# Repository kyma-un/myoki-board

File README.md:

<div align="center">

<picture>
  <source media="(prefers-color-scheme: dark)" srcset="assets/myoki-logo-white.png">
  
</picture>

<p>
  <sub>MAKE YOUR OWN KALMAN IMPLEMENTATION</sub>
</p>

</div>

---

MYOKI es una IMU modular y de código abierto para aprender filtros de Kalman en la asignatura de **Sensores y Actuadores**. Está basada en MYOSA del IEEE Sensors Council.

<div align="center">
  
</div>

## Qué es MYOKI

MYOKI es un *stack* de tres PCB cuadradas de 38.1 mm que se apilan con conectores hembra de 2.54 mm:

| Capa | Proyecto KiCad | Componente principal | Función |
| --- | --- | --- | --- |
| Base | [`myoki-mini-esp32-base`](hardware/myoki-mini-esp32-base) | ESP32-C3 SuperMini | MCU, alimentación (5 V / 3.3 V) y bus I²C / SPI |
| Capa IMU | [`myoki-bmi160-layer`](hardware/myoki-bmi160-layer) | GY-BMI160 | Acelerómetro + giróscopo de 6 ejes |
| Capa magnetómetro | [`myoki-gy271-layer`](hardware/myoki-gy271-layer) | GY-271 | Magnetómetro de 3 ejes |

El dibujo de ejes de la tapa marca la orientación del sistema de referencia de la placa (**+X**, **+Y** y **+Z** saliendo de la placa).

<div align="center">

</div>

### Placa base ESP32-C3

<table>
  <tr>
    <td align="center"></td>
    <td align="center"></td>
  </tr>
  <tr>
    <td align="center"><sub>Ensamblada</sub></td>
    <td align="center"><sub>PCB desnuda</sub></td>
  </tr>
</table>

La base expone los dos buses a las capas de sensores:

| Conector | Pin 1 | Pin 2 | Pin 3 | Pin 4 |
| --- | --- | --- | --- | --- |
| **J1** (SPI) | MOSI | MISO | CS | GND |
| **J2** (I²C) | SDA | SCL | VCC | GND |

El ESP32-C3 SuperMini se monta con el puerto USB-C hacia el borde marcado en la serigrafía.

## Estructura del repositorio

```text
myoki-board/
├── assets/                     Logos y arte gráfico
│   ├── myoki-design-top.png    Diseño de la tapa (acrílico)
│   ├── myoki-logo-banner.png   Banner para documentación
│   ├── myoki-logo-white.png    Logo transparente para fondos oscuros
│   ├── myoki-logo-navy.png     Logo transparente para fondos claros
│   └── renders/                Renders de la carcasa y las PCB
├── hardware/                   Fuentes de diseño (KiCad 10)
│   ├── lib/                    Librería propia "myoky-lib"
│   │   ├── myoky-lib.kicad_sym     Símbolos
│   │   ├── myoky-lib.pretty/       Footprints
│   │   ├── myoky-lib.3dshapes/     Modelos 3D (STEP)
│   │   └── vendor/                 Archivos originales de los fabricantes
│   ├── myoki-mini-esp32-base/  PCB base con ESP32-C3
│   ├── myoki-bmi160-layer/     PCB del BMI160
│   └── myoki-gy271-layer/      PCB del GY-271
└── manufacturing/              Todo lo necesario para fabricar
    ├── bom/                    Lista de materiales (myoki-bom.xlsx)
    ├── gerbers/                Gerbers + drill por placa y .zip listos para enviar
    └── enclosure/              Carcasa: STL para impresión 3D y DXF para corte láser
```

## Cómo construir una MYOKI

### 1. Fabricar las PCB

Sube cada `.zip` de [`manufacturing/gerbers/`](manufacturing/gerbers) a tu fabricante (JLCPCB, PCBWay, etc.):

| Archivo | Placa |
| --- | --- |
| [`myoki-mini-esp32-base.zip`](manufacturing/gerbers/myoki-mini-esp32-base.zip) | Base ESP32-C3 |
| [`myoki-bmi160-layer.zip`](manufacturing/gerbers/myoki-bmi160-layer.zip) | Capa BMI160 |
| [`myoki-gy271-layer.zip`](manufacturing/gerbers/myoki-gy271-layer.zip) | Capa GY-271 |

Parámetros: 2 capas, FR-4, 1.6 mm, 38.1 × 38.1 mm.

### 2. Comprar los componentes

La lista completa, con costos y links de compra, está en [`manufacturing/bom/myoki-bom.xlsx`](manufacturing/bom/myoki-bom.xlsx). Resumen:

| Cant. | Componente | Placa |
| --- | --- | --- |
| 1 | ESP32-C3 SuperMini | Base |
| 1 | Módulo GY-BMI160 | Capa BMI160 |
| 1 | Módulo GY-271 | Capa GY-271 |
| 3 | Condensador 100 nF, 1206 | Base |
| 1 | Resistencia 330 Ω, 1206 | Base |
| 1 | LED rojo, 2010 (5025 métrico) | Base |
| 6 | Conector hembra 1×04, 2.54 mm | 2 por placa |
| 8 + 8 | Separadores y tornillos M3 | Stack |

### 3. Fabricar la carcasa

| Archivo | Proceso |
| --- | --- |
| [`base_plastic_v03.stl`](manufacturing/enclosure/base_plastic_v03.stl) | Impresión 3D, base |
| [`plastic_case_top.stl`](manufacturing/enclosure/plastic_case_top.stl) | Impresión 3D, tapa |
| [`acrylic_drawing.dxf`](manufacturing/enclosure/acrylic_drawing.dxf) | Corte láser en acrílico, con el [diseño de la tapa](assets/myoki-design-top.png) |

### 4. Ensamblar

1. Suelda los componentes SMD y el ESP32-C3 en la base.
2. Suelda los módulos GY-BMI160 y GY-271 en sus capas.
3. Apila las placas con los conectores de 2.54 mm y fíjalas con los separadores M3.
4. Monta el stack en la carcasa y cierra con la tapa de acrílico.

## Editar el diseño

Abre cualquier `.kicad_pro` dentro de [`hardware/`](hardware) con **KiCad 10**. Cada proyecto incluye sus propias `fp-lib-table` y `sym-lib-table`, que apuntan a `${KIPRJMOD}/../lib`, así que la librería `myoky-lib` y sus modelos 3D se cargan sin configuración extra.

---

<div align="center">

<sub>SUPPORTED BY KYMA UN · Licencia <a href="LICENSE">MIT</a> © 2026</sub>

</div>

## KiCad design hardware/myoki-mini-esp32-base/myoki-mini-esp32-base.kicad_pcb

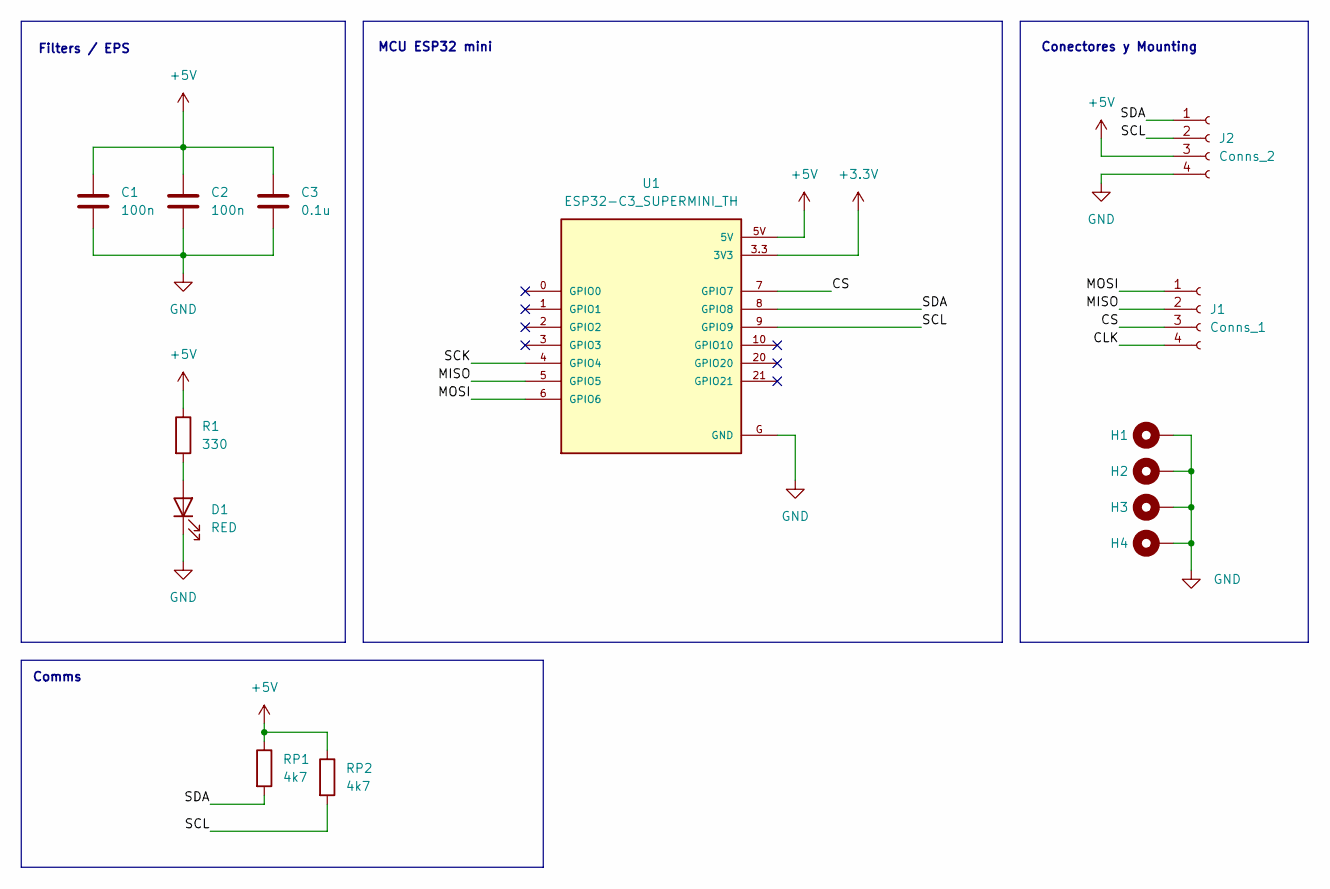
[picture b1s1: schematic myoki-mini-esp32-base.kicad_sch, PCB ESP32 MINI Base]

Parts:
C1, C2: 100n; C_1206_3216Metric_Pad1.33x1.80mm_HandSolder
C3: 0.1u; C_1206_3216Metric_Pad1.33x1.80mm_HandSolder
D1: RED; LED_2010_5025Metric_Pad1.52x2.65mm_HandSolder
H1, H2, H3, H4: MountingHole_Pad; MountingHole_3.2mm_M3_Pad_TopOnly
J1: Conns_1; PinSocket_1x04_P2.54mm_Vertical
J2: Conns_2; PinSocket_1x04_P2.54mm_Vertical
R1: 330; R_1206_3216Metric_Pad1.30x1.75mm_HandSolder
RP1, RP2: 4k7; R_1206_3216Metric_Pad1.30x1.75mm_HandSolder
U1: ESP32-C3_SUPERMINI_TH; MODULE_ESP32-C3_SUPERMINI_TH

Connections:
+3.3V: U1.3.3 (3V3)
+5V: C1.1, C2.1, C3.1, J2.3, R1.1, RP1.1, RP2.1, U1.5V
/CLK: J1.4
/CS: J1.3, U1.7 (GPIO7)
/MISO: J1.2, U1.5 (GPIO5)
/MOSI: J1.1, U1.6 (GPIO6)
/SCK: U1.4 (GPIO4)
/SCL: J2.2, RP2.2, U1.9 (GPIO9)
/SDA: J2.1, RP1.2, U1.8 (GPIO8)
GND: C1.2, C2.2, C3.2, D1.1 (K), H1.1 (1_1), H2.1 (1_1), H3.1 (1_1), H4.1 (1_1), J2.4, U1.G (GND)
unnamed: D1.2 (A), R1.2

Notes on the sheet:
MCU ESP32 mini
Conectores y Mounting
Filters / EPS
Comms

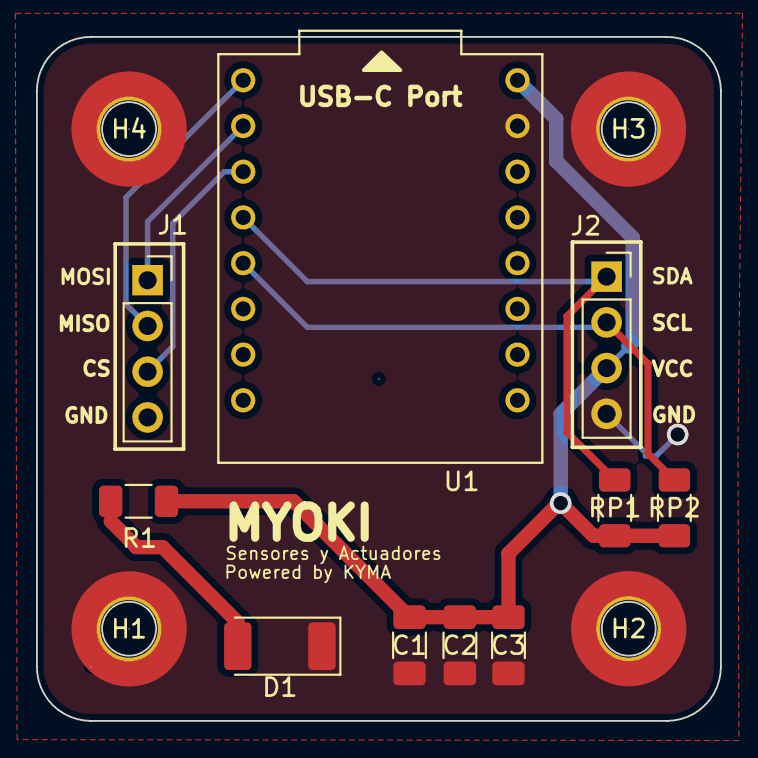
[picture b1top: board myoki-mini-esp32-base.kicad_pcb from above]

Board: 2 copper layers, 38.0 x 38.0 mm, 14 parts (0 on the bottom side), 8 nets.

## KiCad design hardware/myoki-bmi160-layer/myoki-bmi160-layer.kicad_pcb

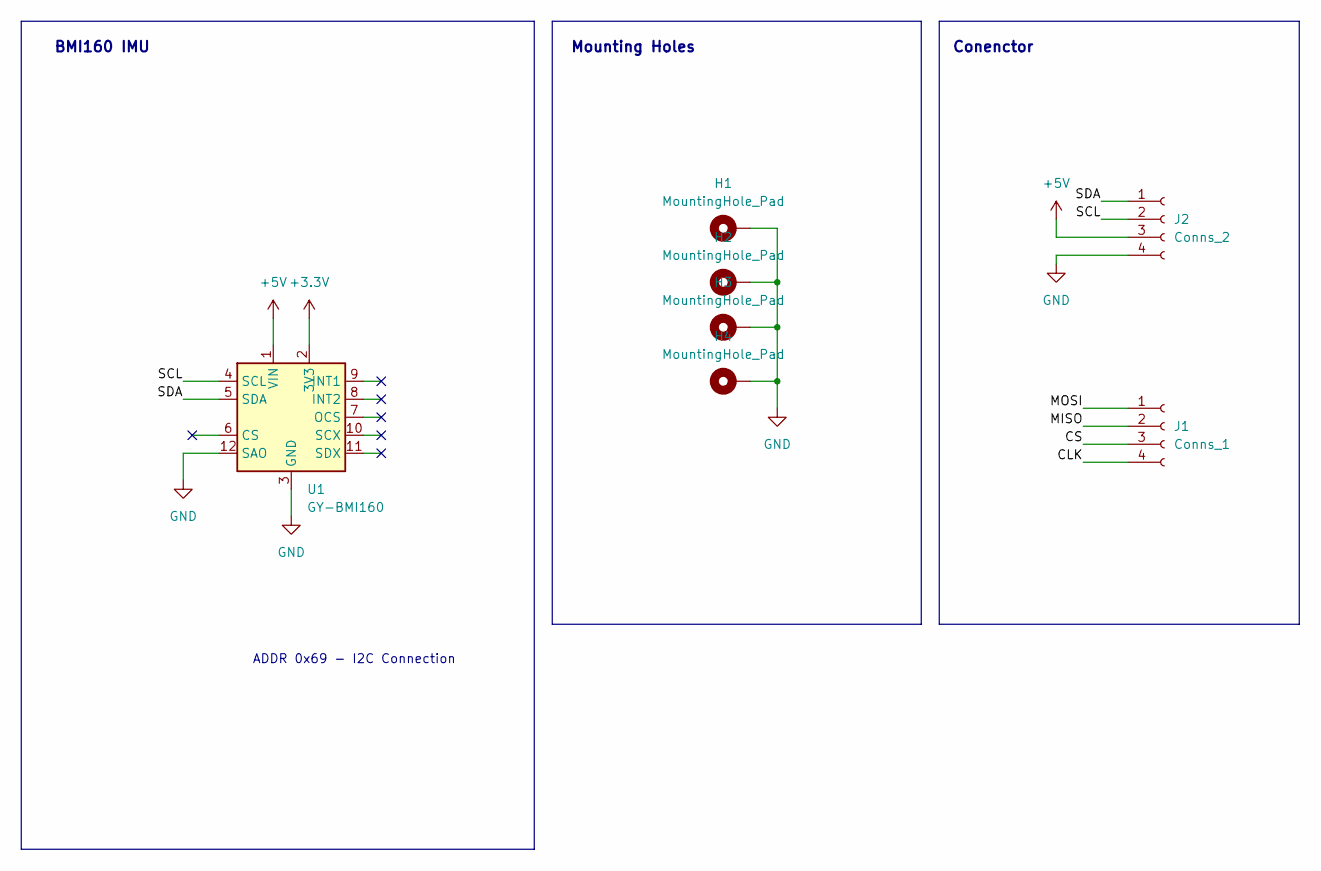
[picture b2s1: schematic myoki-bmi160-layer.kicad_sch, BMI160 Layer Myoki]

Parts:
H1, H2, H3, H4: MountingHole_Pad; MountingHole_3.2mm_M3_DIN965_Pad
J1: Conns_1; PinSocket_1x04_P2.54mm_Vertical
J2: Conns_2; PinSocket_1x04_P2.54mm_Vertical
U1: GY-BMI160

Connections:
+3.3V: U1.2 (3V3)
+5V: J2.3, U1.1 (VIN)
/CLK: J1.4
/CS: J1.3
/MISO: J1.2
/MOSI: J1.1
/SCL: J2.2, U1.4 (SCL)
/SDA: J2.1, U1.5 (SDA)
GND: H1.1 (1_1), H2.1 (1_1), H3.1 (1_1), H4.1 (1_1), J2.4, U1.3 (GND), U1.12 (SAO)

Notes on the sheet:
Mounting Holes
ADDR 0x69 - I2C Connection
Conenctor
BMI160 IMU

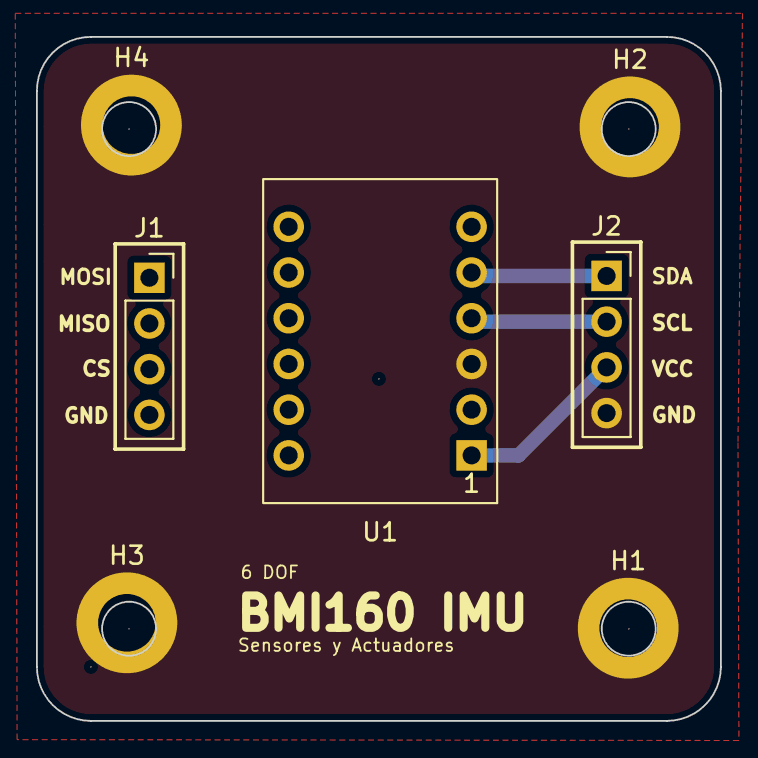
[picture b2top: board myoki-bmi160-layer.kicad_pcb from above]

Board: 2 copper layers, 38.0 x 38.0 mm, 7 parts (0 on the bottom side), 4 nets.

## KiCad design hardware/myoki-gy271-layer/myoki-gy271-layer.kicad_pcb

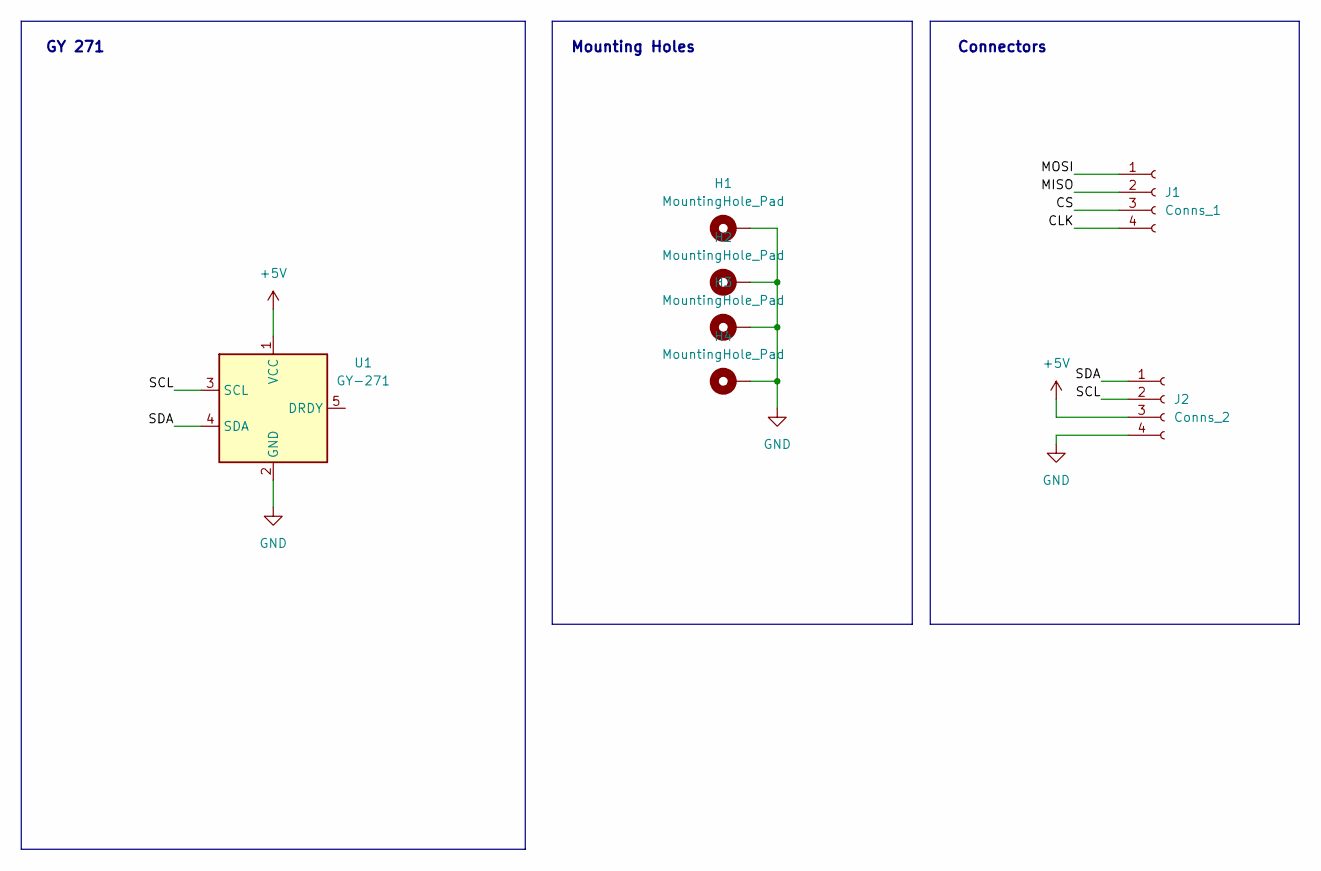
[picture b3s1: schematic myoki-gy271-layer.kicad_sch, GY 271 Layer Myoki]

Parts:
H1, H2, H3, H4: MountingHole_Pad; MountingHole_3.2mm_M3_DIN965_Pad
J1: Conns_1; PinSocket_1x04_P2.54mm_Vertical
J2: Conns_2; PinSocket_1x04_P2.54mm_Vertical
U1: GY-271

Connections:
+5V: J2.3, U1.1 (VCC)
/CLK: J1.4
/CS: J1.3
/MISO: J1.2
/MOSI: J1.1
/SCL: J2.2, U1.3 (SCL)
/SDA: J2.1, U1.4 (SDA)
GND: H1.1 (1_1), H2.1 (1_1), H3.1 (1_1), H4.1 (1_1), J2.4, U1.2 (GND)

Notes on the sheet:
Mounting Holes
GY 271
Connectors

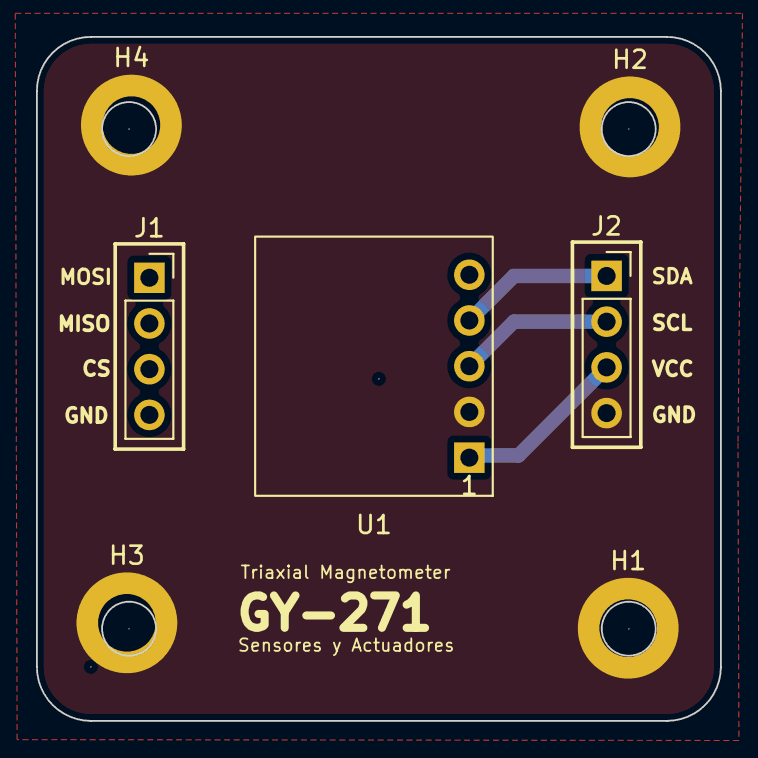
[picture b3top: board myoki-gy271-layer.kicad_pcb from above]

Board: 2 copper layers, 38.0 x 38.0 mm, 7 parts (0 on the bottom side), 4 nets.
